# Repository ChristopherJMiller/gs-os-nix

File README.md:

# gs-os-nix

Running **Nix on an Apple IIgs** under GS/OS, with a custom FPGA accelerator card
supplying the three things a 1986 machine lacks: memory capacity, hashing throughput,
and pointer/search throughput.

The goal is not a tribute. It is an Apple IIgs that computes store paths and `.drv`
hashes **byte-identically to upstream Nix**, evaluating real Nix natively.

## Orientation

| Doc | Read it for |
|---|---|
| [docs/ARCHITECTURE.md](docs/ARCHITECTURE.md) | The machine: what runs where, and why |
| [docs/CARD-ISA.md](docs/CARD-ISA.md) | **Normative** card interface — register map and verbs |
| [docs/HEAP.md](docs/HEAP.md) | **Normative** heap object layout and tags |
| [docs/DECISIONS.md](docs/DECISIONS.md) | Why it's built this way, and what was rejected |
| [docs/REFERENCES.md](docs/REFERENCES.md) | Verified facts with citations — don't re-derive these |
| [docs/RUNNING.md](docs/RUNNING.md) | Getting code onto the emulated IIgs |
| [docs/STATUS.md](docs/STATUS.md) | Layer progress, the roadmap, and how to resume |
| [docs/SOURCES.md](docs/SOURCES.md) | Every external tool and file: where from, its hash, how to find it again |
| [docs/HARDWARE.md](docs/HARDWARE.md) | The physical card: board design, bus interface, capture, and how an agent designs it |

## The one-paragraph version

The Apple IIgs owns everything semantic: lexer, parser, compiler, bytecode VM, lazy
forcing, all primops, string context, the store, derivation logic, GS/OS integration.
The card owns memory capacity and compute-bound kernels, and **never makes a decision
or touches the world**. Linux does nothing at runtime — it only builds the toolchain,
generates golden test fixtures, and runs MAME for CI.

The design's keystone: the IIgs throttles to 1.024 MHz for any `$Cxxx` access, making
one card access cost about the same as one fast-RAM pointer dereference. Therefore
**the bus carries verbs, not data** — and the generational GC boundary *is* the slot
connector, with the nursery in fast RAM and mature space on the card.

## Quick start

```sh
nix develop          # verilator, cocotb, yosys, nextpnr, trellis, cc65, mame
nix develop .#hw     # KiCad 10, SKiDL, Freerouting: the board itself (hw/README.md)
nix flake check      # cocotb suites, lint, synth smoke, conformance scoreboard, hw-* gates
just repl            # type Nix at the VM: each line compiled, run and printed by it, on a2min
```

`apple2gs` ROMs are not redistributable and must be supplied by you, explicitly, as
`ROMPATH` (docs/RUNNING.md "ROMs"); MAME-dependent checks skip without them. Nothing
the gates need is ROM-dependent.

## Licence

gs-os-nix is free software: you can redistribute it and/or modify it under the
terms of the **GNU General Public License, version 3 or (at your option) any later
version** ([LICENSE](LICENSE)). SPDX: `GPL-3.0-or-later`.

Included under their own terms: the tvix corpus in `tests/corpus/tvix/` (GPL-3.0)
and Nix's `derivation.nix` in `tools/nbc/src/` (LGPL-2.1), and `builtins.sort`'s
peeksort in `target/vm/c/prims.c`, ported from Nix's `sort.hh` (LGPL-2.1), which
adapts Sebastian Wild's powersort (MIT; its notice is with the code), and
`builtins.toJSON`'s float formatting in `target/vm/c/float.c`, ported from
nlohmann/json's `to_chars.hpp` (MIT, Florian Loitsch and Niels Lohmann; its notice
is with the code), and `builtins.match` and `split`'s regular expressions in
`target/vm/c/regex.c`, ported from the GNU ISO C++ Library's `<regex>` (GPL-3.0
or later with the GCC Runtime Library Exception, the Free Software Foundation;
its notice is with the code), and `builtins.fromTOML`'s parser in
`target/vm/c/toml.c`, ported from toml11's (MIT, Toru Niina; its notice is with
the code). Not included at all:
ORCA/C, which every build fetches from Byte Works under its own
non-redistributable licence, and the Apple IIgs ROMs, which you supply
([docs/SOURCES.md](docs/SOURCES.md)).

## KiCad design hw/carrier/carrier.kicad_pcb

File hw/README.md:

<!-- SPDX-License-Identifier: CERN-OHL-S-2.0 -->

# hw — the physical card

The open-hardware side of gs-os-nix: Apple II slot cards designed as code. SKiDL
writes the netlist, scripts place and route the board in KiCad 10, and mutation-proven
gates check it. The design, its decisions and the owner's review checklist are in
[docs/HARDWARE.md](../docs/HARDWARE.md).

## The bus carrier

The first board is a development carrier, not the release card (HW-3). It holds the
**bus section** that the integrated card will reuse unchanged: the Apple II edge
fingers, level translators, input and listen-only buffers, open-drain outputs and the
reset hold. The data translator is an **SN74LVCR2245A**, whose outputs have 26 Ω series
resistors built in, to tame the overshoot on the Apple bus (HW-16). A DDR2 SODIMM-200
socket takes an **iCESugar-Pro** module (LFE5U-25F, 32 MB SDRAM).

| Top | Bottom |
|---|---|
|  |  |

The silkscreen carries the name, the open-source-hardware gear and, in the band above J2 that
the module covers once it is plugged in, an Apple II and the NixOS snowflake in ASCII. A
script places the reference designators clear of pads and other silkscreen; the 8 it finds no
room for are named on the fab layer and in the interactive BOM.

- 4 layers: signals on the outside, a ground plane and a 3.3 V plane inside (HW-17).
  80 mm × 69.5 mm above the fingers. It fits any slot, 1–7.
- Every slot pin loads the bus with at most 15 pF, Apple's limit (`hw-load`; the worst is
  14.3 pF).
- The module lies flat over the empty band above the socket. Its own USB programs it
  and carries capture readout (HW-13). The carrier adds a UART header (J4) and two
  jumpers: SAFE (JP1) and the reset-hold bypass (JP2).
- Power: slot +5 V → polyfuse F1 → Schottky D1 → module; an AP2112K makes the
  translators' 3.3 V from the module side (HW-14).
- DRC is clean (0 errors, 0 unconnected, no warnings), and the board matches the netlist pin
  for pin.

**How it's routed** (HW-18). The buses are planned first: each FPGA-side bus takes J2
contacts in the order of its translator's pins, so its nets never cross. Our own router,
`bus_route.py`, then lays those buses, the clocks and most of the 5 V rails, deterministically, and
locks them. Freerouting 2.5.0 routes the remaining nets, an A* finisher joins whatever it
leaves, and every step gives the same copper on every run of the flake's pinned inputs (KiCad 10.0.6,
the Freerouting 2.5.0 jar on JDK 25, 6 router threads, the `route` recipe's 20 passes; checked on
one machine): `just -f hw/justfile repro` routes the board again and checks that it does. Bumping
nixpkgs or the jar means running `route` and `repro` again.

**Status:** designed, routed and gated. It is not yet fabricated, and not yet tested in
a IIgs. Rev A, the integrated ECP5 card, is ordered only after this carrier has run in
a real machine (HW-9).

## Layout

| Path | What |
|---|---|
| `src/` | SKiDL subcircuits; `slot_bus.py` is the bus section |
| `carrier/` | The carrier: `top.py`, `pins.toml` (the FPGA pin map), `placement.toml`, the module's SODIMM map, `artwork.toml` (the silkscreen art), the routed `carrier.kicad_pcb` |
| `lib/` | Generated: `gsnix.pretty/` (the slot fingers and the SODIMM socket) and `gsnix.3dshapes/` (an approximate socket body, for renders only) |
| `tools/` | Board builder, bus planner and router, the route, the silkscreen, fab export, and the `check_*.py` gates |
| `tests/` | The tools' tests (`hw-tests`) |
| `img/` | The pictures above, refreshed with `just -f hw/justfile readme-images` |

## Using it

```sh
nix develop .#hw
just -f hw/justfile check          # every gate, each selftest first
just -f hw/justfile fab            # gerbers, BOM, CPL, renders in build/hw/fab
nix build .#hw-carrier-fab         # the same order package, from Nix
just -f hw/justfile artwork        # (re)apply the silkscreen art and place the designators
just -f hw/justfile route          # route the board again (about 15 min); then `artwork`
just -f hw/justfile repro          # check that `route` gives the committed copper (as long)

nix develop .#hw-render            # optional: the hw shell plus KiCad's 3D models (a big download)
just -f hw/justfile readme-images  # the 3D renders in hw/img
```

`nix flake check` runs the same gates as `hw-*` checks. It and `nix develop .#hw` never
fetch the 3D model library; only `.#hw-render` does.

## Credits

- The Nix snowflake in the silkscreen art is drawn after the NixOS logo (CC-BY 4.0,
  [NixOS/branding](https://github.com/NixOS/branding)).
- The open-source-hardware gear is the silkscreen symbol from KiCad's footprint library
  (`Symbol.pretty`, CC-BY-SA 4.0 with the library's design exception).
- The 3D renders use KiCad's 3D model library, and our own approximate socket body.
- [Freerouting](https://github.com/freerouting/freerouting) (GPL-3.0) routes the nets our
  bus router leaves; the flake pins its 2.5.0 release.

## Licence

Board files are **CERN-OHL-S-2.0** ([LICENSE](LICENSE)). The tools, the tests and the
RTL are GPL-3.0-or-later, like the rest of the repo.

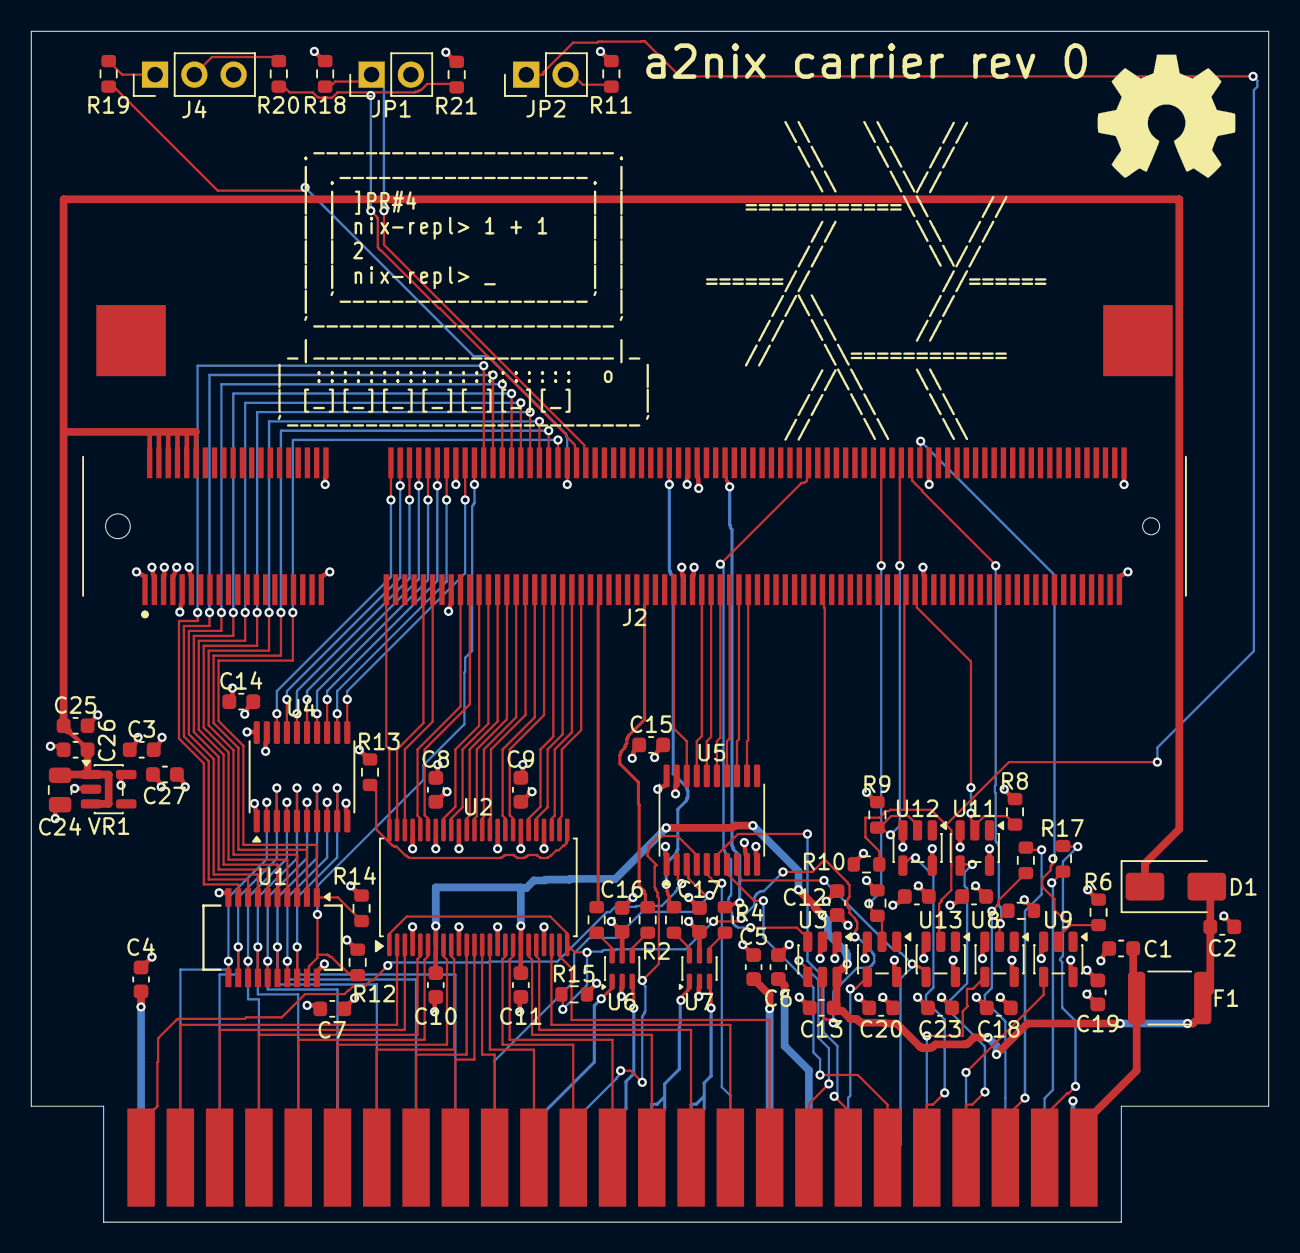
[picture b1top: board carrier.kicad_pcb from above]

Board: 4 copper layers, 80.0 x 77.0 mm, 69 parts (0 on the bottom side), 117 nets.

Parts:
C1, C4, C5, C6, C7, C8, C9, C10, C11, C12, C13, C14, C15, C16, C17, C18, C19, C20, C21, C22, C23, C25: 100nF; C_0603_1608Metric
C2, C3, C26, C27: 10uF; C_0603_1608Metric
C24: 22uF; C_0805_2012Metric
D1: B220A; D_SMA
F1: 500mA; Fuse_1812_4532Metric
J1: Apple II slot; AppleII_Slot_Edge
J2: iCESugar-Pro; SODIMM200_DDR2
J4: UART; PinHeader_1x03_P2.54mm_Vertical
JP1: SAFE; PinHeader_1x02_P2.54mm_Vertical
JP2: RESET hold off; PinHeader_1x02_P2.54mm_Vertical
R1, R2, R3, R4, R16, R17: 0; R_0603_1608Metric
R5, R6, R7, R8, R9, R12, R13, R14, R15, R18, R21: 10k; R_0603_1608Metric
R10: 4.7k; R_0603_1608Metric
R11: 1k; R_0603_1608Metric
R19, R20: 100; R_0603_1608Metric
U1: SN74LVCR2245A; SSOP-20_3.9x8.7mm_P0.635mm
U2: 74ALVC164245; TSSOP-48_6.1x12.5mm_P0.5mm
U3: SN74LVC1T45; SOT-23-6
U4, U5: 74LVC541; TSSOP-20_4.4x6.5mm_P0.65mm
U6, U7: 74LVC2G17; SOT-363_SC-70-6
U8, U9, U10, U11, U12, U13: 74LVC1G07; SOT-23-5
VR1: AP2112K-3.3; SOT-23-5

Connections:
+3V3: C3.1, C7.1, C8.1, C9.1, C12.1, C14.1, C15.1, C16.1, C17.1, C18.1, C19.1, C20.1, C21.1, C22.1, C23.1, C27.1, R5.2, R6.2, R7.2, R8.2, R9.2, R11.2, R12.2, R13.2, R18.2, R21.2, U1.20, U2.31, U2.42, U3.1, U4.20, U5.20, U6.5, U7.5, U8.5, U9.5, U10.5, U11.5, U12.5, U13.5, VR1.5
+5V: C2.1, C10.1, C11.1, C13.1, D1.2, F1.2, U2.7, U2.18, U3.6
+5V_MOD: C24.1, C25.1, C26.1, D1.1, J2.2, J2.4, J2.6, J2.8, J2.10, J2.12, VR1.1, VR1.3
+5V_SLOT: C1.1, F1.1, J1.25
+12V_SLOT: C4.1, J1.50
-5V_SLOT: C5.1, J1.34
-12V_SLOT: C6.1, J1.33
CLK_7M_BUF: R4.1, U7.4
CLK_PH0_BUF: R1.1, U6.6
CLK_PH1_BUF: R2.1, U6.4
CLK_Q3_BUF: R3.1, U7.6
GND: C1.2, C2.2, C3.2, C4.2, C5.2, C6.2, C7.2, C8.2, C9.2, C10.2, C11.2, C12.2, C13.2, C14.2, C15.2, C16.2, C17.2, C18.2, C19.2, C20.2, C21.2, C22.2, C23.2, C24.2, C25.2, C26.2, C27.2, J1.26, J2.1, J2.3, J2.5, J2.7, J2.9, J2.11, J2.39, J2.40, J2.55, J2.56, J2.105, J2.106, J2.107, J2.108, J2.157, J2.158, J2.199, J2.200, J4.3, JP1.2, R10.2, R14.2, R15.2, U1.10, U2.4, U2.10, U2.15, U2.21, U2.28, U2.34, U2.39, U2.45, U3.2, U4.1, U4.10, U4.19, U5.1, U5.9, U5.10, U5.19, U6.2, U7.2, U8.3, U9.3, U10.3, U11.3, U12.3, U13.3, VR1.2
JP2_3V3: JP2.2, R11.1
SLOT_7M: J1.36, U7.3
SLOT_A0: J1.2, U2.2
SLOT_A1: J1.3, U2.3
SLOT_A2: J1.4, U2.5
SLOT_A3: J1.5, U2.6
SLOT_A4: J1.6, U2.8
SLOT_A5: J1.7, U2.9
SLOT_A6: J1.8, U2.11
SLOT_A7: J1.9, U2.12
SLOT_A8: J1.10, U2.13
SLOT_A9: J1.11, U2.14
SLOT_A10: J1.12, U2.16
SLOT_A11: J1.13, U2.17
SLOT_A12: J1.14, U2.19
SLOT_A13: J1.15, U2.20
SLOT_A14: J1.16, U2.22
SLOT_A15: J1.17, U2.23
SLOT_D0: J1.49, U1.11, U4.2
SLOT_D1: J1.48, U1.12, U4.3
SLOT_D2: J1.47, U1.13, U4.4
SLOT_D3: J1.46, U1.14, U4.5
SLOT_D4: J1.45, U1.15, U4.6
SLOT_D5: J1.44, U1.16, U4.7
SLOT_D6: J1.43, U1.17, U4.8
SLOT_D7: J1.42, U1.18, U4.9
SLOT_DEVSEL_N: J1.41, U5.3
SLOT_DMA_IN: J1.27, R17.1
SLOT_DMA_N: J1.22, U11.4
SLOT_DMA_OUT: J1.24, R17.2
SLOT_INH_N: J1.32, U10.4
SLOT_INT_IN: J1.28, R16.1
SLOT_INT_OUT: J1.23, R16.2
SLOT_IOSEL_N: J1.1, U5.2
SLOT_IOSTRB_N: J1.20, U5.7
SLOT_IRQ_N: J1.30, U8.4
SLOT_M2B0: J1.35, U5.5
SLOT_M2SEL_N: J1.39, U5.4
SLOT_NMI_N: J1.29, U9.4
SLOT_PH0: J1.40, U6.1
SLOT_PH1: J1.38, U6.3
SLOT_Q3: J1.37, U7.1
SLOT_RDY: J1.21, U12.4
SLOT_RESET_N: J1.31, U5.8, U13.4
SLOT_RW: J1.18, U3.4
SLOT_SYNC_N: J1.19, U5.6
UART_RX: J4.2, R20.2
UART_TX: J4.1, R19.2
safe_n: J2.84, JP1.1, R18.1
slot_7m: J2.114, R4.2
slot_a0: J2.49, U2.47
slot_a1: J2.51, U2.46
slot_a2: J2.57, U2.44
slot_a3: J2.59, U2.43
slot_a4: J2.61, U2.41
slot_a5: J2.63, U2.40
slot_a6: J2.65, U2.38
slot_a7: J2.67, U2.37
slot_a8: J2.69, U2.36
slot_a9: J2.71, U2.35
slot_a10: J2.73, U2.33
slot_a11: J2.75, U2.32
slot_a12: J2.77, U2.30
slot_a13: J2.79, U2.29
slot_a14: J2.81, U2.27
slot_a15: J2.83, U2.26
slot_a_dir: J2.135, R15.1, U2.1, U2.24, U3.5
slot_a_oe_n: J2.41, R13.1, U2.25, U2.48
slot_d0: J2.62, U1.9
slot_d1: J2.64, U1.8
slot_d2: J2.66, U1.7
slot_d3: J2.68, U1.6
slot_d4: J2.70, U1.5
slot_d5: J2.72, U1.4
slot_d6: J2.74, U1.3
slot_d7: J2.76, U1.2
slot_d_dir: J2.78, R14.1, U1.1
slot_d_oe_n: J2.60, R12.1, U1.19
slot_devsel_n: J2.109, U5.17
slot_dl0: J2.42, U4.18
slot_dl1: J2.44, U4.17
slot_dl2: J2.46, U4.16
slot_dl3: J2.48, U4.15
slot_dl4: J2.50, U4.14
slot_dl5: J2.52, U4.13
slot_dl6: J2.54, U4.12
slot_dl7: J2.58, U4.11
slot_dma_n_o: J2.155, R8.1, U11.2
slot_inh_n_o: J2.148, R7.1, U10.2
slot_iosel_n: J2.103, U5.18
slot_iostrb_n: J2.117, U5.13
slot_irq_n_o: J2.154, R5.1, U8.2
slot_m2b0: J2.113, U5.15
slot_m2sel_n: J2.111, U5.16
slot_nmi_n_o: J2.156, R6.1, U9.2
slot_ph0: J2.87, R1.2
slot_ph1: J2.97, R2.2
slot_q3: J2.102, R3.2
slot_rdy_o: J2.152, R9.1, U12.2
slot_reset_n: J2.119, U5.12
slot_reset_n_o: J2.153, JP2.1, R10.1, U13.2
slot_rw: J2.132, U3.3
slot_sync_n: J2.115, U5.14
uart_rx: J2.82, R20.1, R21.1
uart_tx: J2.80, R19.1

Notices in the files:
parts and their libraries:
Apple II peripheral slot edge fingers, 2 x 25 at 2.54 mm: pins 1-25 on F.Cu from the front, pin 51-n behind pin n on B.Cu; origin at the middle of the tab's bottom edge. Generated by hw/tools/footprints.py. SPDX-License-Identifier: CERN-OHL-S-2.0
